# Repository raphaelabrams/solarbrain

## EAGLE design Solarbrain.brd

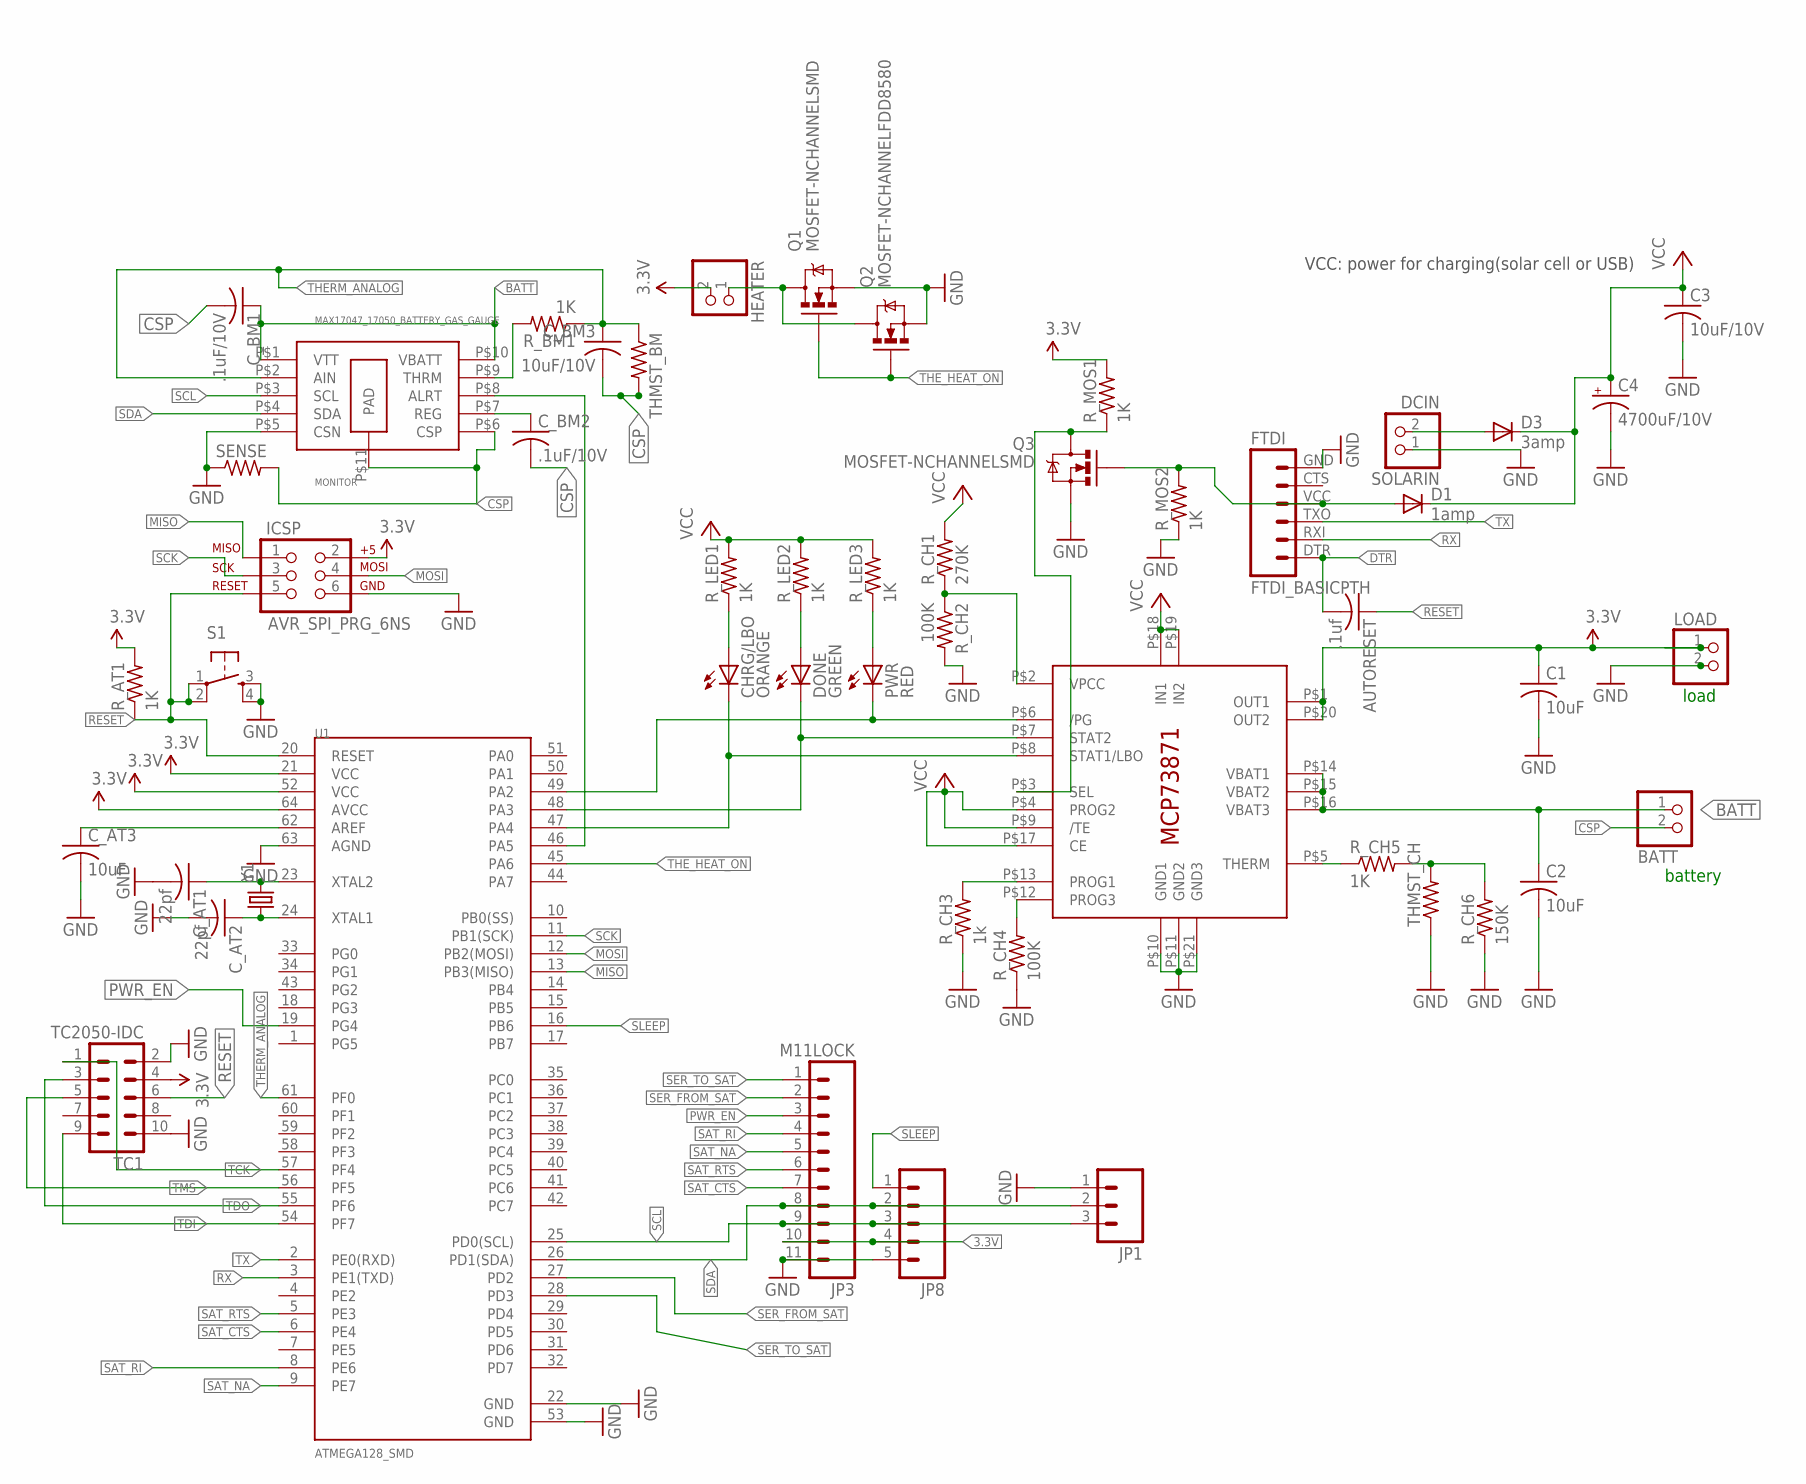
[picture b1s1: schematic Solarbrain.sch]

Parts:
AUTORESET: .1uf; C0603
BATT: JST_2PIN-SMT-RA; JST-PH-2-SMT-RA
C1: 10uF; C0603
C2: 10uF; C0805K
C3: 10uF/10V; C0603
C4: 4700uF/10V; PANASONIC_G
CHRG/LBO: ORANGE; CHIP-LED0603
C_AT1: 22pf; C0603K
C_AT2: 22pf; C0603
C_AT3: 10uF; C0805K
C_BM1, C_BM2: .1uF/10V; C0603
C_BM3: 10uF/10V; C0603
D1: 1amp; SMA-DIODE
D3: 3amp; SMA-DIODE
DONE: GREEN; CHIP-LED0603
FTDI: FTDI_BASICPTH; FTDI_BASIC
HEATER: HEADER-1X2ROUND; 1X02_ROUND
IC1: MCP73871; QFN20_4MM
ICSP: AVR_SPI_PRG_6NS; 2X3-NS
JP1: M03PTH; 1X03
JP3: M11LOCK; 1X11_LOCK
JP8: M05LOCK; 1X05_LOCK
LOAD: HEADER-1X2ROUND; 1X02_ROUND
MONITOR: MAX17047_17050_BATTERY_GAS_GAUGE; TDFN_10_3X3MM
PWR: RED; CHIP-LED0603
Q1, Q3: MOSFET-NCHANNELSMD; SOT23-3
Q2: MOSFET-NCHANNELFDD8580; DPAK
R_AT1: 1K; R0603
R_BM1: 1K; R0603
R_CH1: 270K; R0603
R_CH2, R_CH4: 100K; R0603
R_CH3: 1k; R0603
R_CH5: 1K; R0603
R_CH6: 150K; R0603
R_LED1, R_LED2, R_LED3: 1K; R0603
R_MOS1, R_MOS2: 1K; R0603
S1: TAC_SWITCHSMD; TACTILE_SWITCH_SMD
SENSE: R-US_R3225; R3225
SOLARIN: DCIN; 1X02_ROUND
TC1: TC2050-IDC
THMST_BM: R-US_R0603; R0603
THMST_CH: R-US_R0603; R0603
U1: ATMEGA128_SMD; TQFP64
Y1: CRYSTAL5X3; CRYSTAL-SMD-5X3

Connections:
3.3V: C1.1, HEATER.2, IC1.P$1 (OUT1), IC1.P$20 (OUT2), ICSP.2, JP3.10, JP8.4, LOAD.1, R_AT1.2, R_MOS1.2, TC1.4, U1.21 (VCC), U1.52 (VCC), U1.64 (AVCC)
#PG: IC1.P$6 (/PG), PWR.C, U1.49 (PA2)
BATT: BATT.1 (2), C2.1, C_BM1.1, IC1.P$14 (VBAT1), IC1.P$15 (VBAT2), IC1.P$16 (VBAT3), MONITOR.P$1 (VTT), MONITOR.P$10 (VBATT)
CSP: BATT.2 (1), C_BM1.2, C_BM2.2, C_BM3.2, MONITOR.P$6 (CSP), MONITOR.P$11 (PAD), SENSE.2, THMST_BM.2
DTR: AUTORESET.2, FTDI.DTR (1)
GND: C1.2, C2.2, C3.2, C4.-, C_AT1.2, C_AT2.2, C_AT3.2, FTDI.GND (6), IC1.P$10 (GND1), IC1.P$11 (GND2), IC1.P$21 (GND3), ICSP.6, JP1.1, JP3.11, JP8.5, LOAD.2, MONITOR.P$5 (CSN), Q1.2 (S), Q2.3 (S), Q3.2 (S), R_CH2.2, R_CH3.1, R_CH4.1, R_CH6.1, R_MOS2.1, S1.3, S1.4, SENSE.1, SOLARIN.1, TC1.2, TC1.10, THMST_CH.1, U1.22 (GND), U1.53 (GND), U1.63 (AGND)
MISO: ICSP.1, U1.13 (PB3(MISO))
MOSI: ICSP.4, U1.12 (PB2(MOSI))
unnamed: D1.A, FTDI.VCC (4), Q3.1 (G), R_MOS2.2
unnamed: C_AT1.1, U1.23 (XTAL2), Y1.3 (2)
unnamed: IC1.P$5 (THERM), R_CH5.1
unnamed: R_CH5.2, R_CH6.2, THMST_CH.2
unnamed: C_AT2.1, U1.24 (XTAL1), Y1.1
unnamed: CHRG/LBO.A, R_LED1.1
unnamed: DONE.A, R_LED2.1
unnamed: PWR.A, R_LED3.1
unnamed: MONITOR.P$8 (ALRT), U1.46 (PA5)
unnamed: C_AT3.1, U1.62 (AREF)
unnamed: HEATER.1, Q1.3 (D), Q2.4 (D)
unnamed: MONITOR.P$9 (THRM), R_BM1.2
unnamed: D3.A, SOLARIN.2
unnamed: C_BM2.1, MONITOR.P$7 (REG)
PROG1: IC1.P$13 (PROG1), R_CH3.2
PROG3: IC1.P$12 (PROG3), R_CH4.2
PWR_EN: JP3.3, U1.19 (PG4)
RESET: AUTORESET.1, ICSP.5, R_AT1.1, S1.1, S1.2, TC1.6, U1.20 (RESET)
RX: FTDI.RXI (2), U1.3 (PE1(TXD))
SAT_CTS: JP3.7, U1.6 (PE4)
SAT_NA: JP3.5, U1.9 (PE7)
SAT_RI: JP3.4, U1.8 (PE6)
SAT_RTS: JP3.6, U1.5 (PE3)
SCK: ICSP.3, U1.11 (PB1(SCK))
SCL: JP1.3, JP3.9, JP8.3, MONITOR.P$3 (SCL), U1.25 (PD0(SCL))
SDA: JP1.2, JP3.8, JP8.2, MONITOR.P$4 (SDA), U1.26 (PD1(SDA))
SEL: IC1.P$3 (SEL), Q3.3 (D), R_MOS1.1
SER_FROM_SAT: JP3.2, U1.27 (PD2)
SER_TO_SAT: JP3.1, U1.28 (PD3)
SLEEP: JP8.1, U1.16 (PB6)
STAT1: CHRG/LBO.C, IC1.P$8 (STAT1/LBO), U1.47 (PA4)
STAT2: DONE.C, IC1.P$7 (STAT2), U1.48 (PA3)
TCK: TC1.1, U1.57 (PF4)
TDI: TC1.9, U1.54 (PF7)
TDO: TC1.3, U1.55 (PF6)
THERM_ANALOG: C_BM3.1, MONITOR.P$2 (AIN), R_BM1.1, THMST_BM.1, U1.61 (PF0)
THE_HEAT_ON: Q1.1 (G), Q2.1 (G), U1.45 (PA6)
TMS: TC1.5, U1.56 (PF5)
TX: FTDI.TXO (3), U1.2 (PE0(RXD))
VCC: C3.1, C4.+, D1.C, D3.C, IC1.P$4 (PROG2), IC1.P$9 (/TE), IC1.P$17 (CE), IC1.P$18 (IN1), IC1.P$19 (IN2), R_CH1.2, R_LED1.2, R_LED2.2, R_LED3.2
VPCC: IC1.P$2 (VPCC), R_CH1.1, R_CH2.1

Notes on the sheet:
load
battery
VCC: power for charging(solar cell or USB)

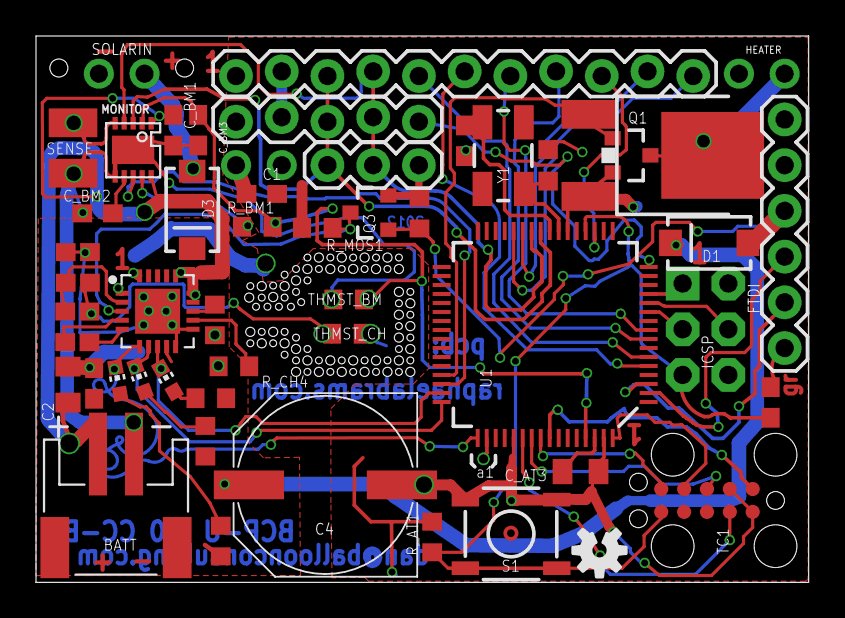
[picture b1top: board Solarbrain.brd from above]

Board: 2 copper layers, 42.9 x 30.4 mm, 51 parts (0 on the bottom side), 49 nets.

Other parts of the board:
U$1: OSHW-LOGO-S

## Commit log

2012-12-20 first commit. Made board, schematic and project file. Probably can delete project file.
2012-12-20 fixed a broken connection, clarification on schematic
2012-12-20 minor tweaks on board, added a via to get to an extra IO pin (pa1)
2013-01-02 major tweak list
    issues addressed:
    * Atmega Circuit
    1. PWR_EN from sat connector net not connected to any I/O pin on
    ATMega
    * Fuel Gauge Circuit
    1. VBATT (BATT) voltage sense trace for the MAX17047 should be a

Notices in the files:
Solarbrain.brd:
BCP-U 1.0 CC-BY
parts and their libraries:
SparkFun2011: Licensing: CC v3.0 Share-Alike You are welcome to use this library for commercial purposes.
